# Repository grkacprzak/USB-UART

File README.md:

# USB-UART
industrial grade USB to UART converter

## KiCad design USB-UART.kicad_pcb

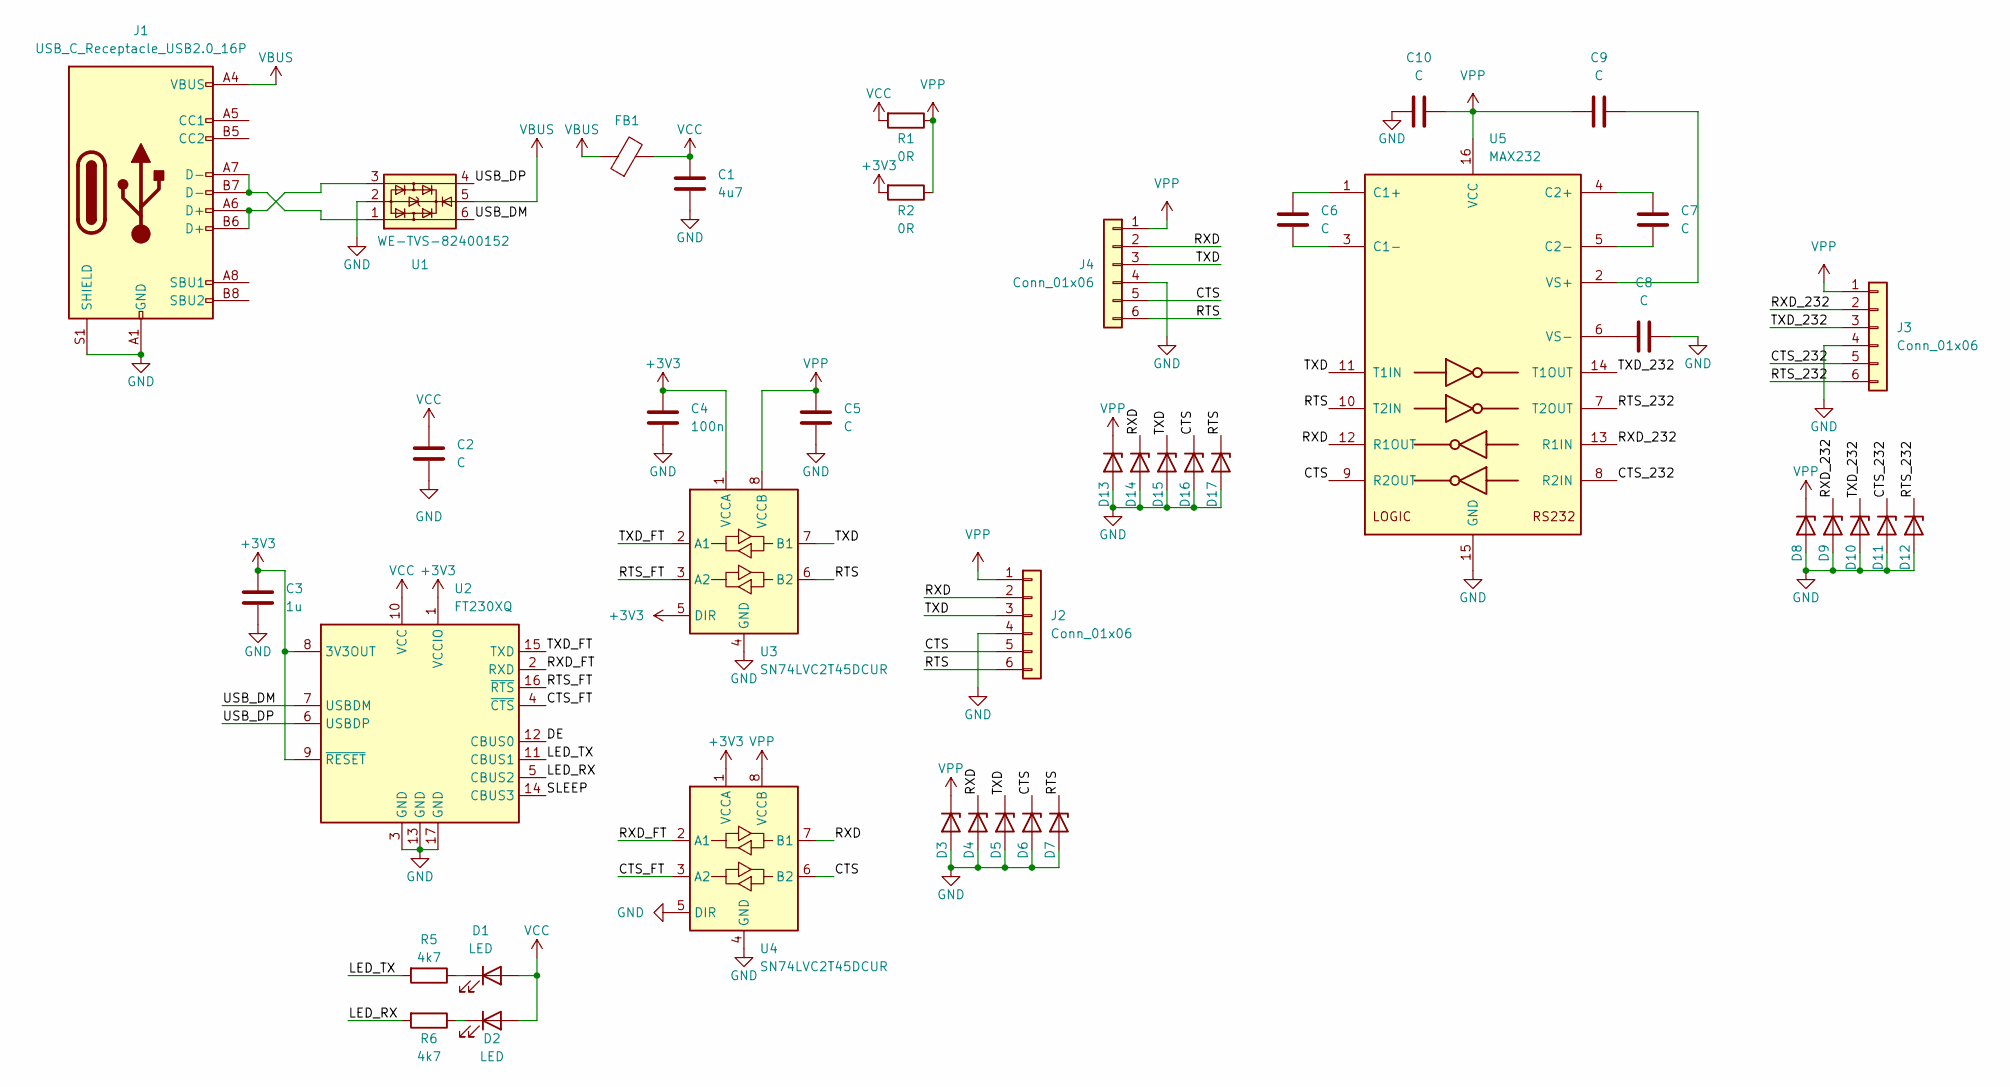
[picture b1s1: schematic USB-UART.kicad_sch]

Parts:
C1: 4u7; C_0402_1005Metric
C2, C5, C6, C7, C8, C9, C10: C; C_0402_1005Metric
C3: 1u; C_0402_1005Metric
C4: 100n; C_0402_1005Metric
D1, D2: LED; LED_0603_1608Metric
D3, D4, D5, D6, D7, D8, D9, D10, D11, D12, D13, D14, D15, D16, D17: D_Zener; D_SOD-523
FB1: FerriteBead; L_0402_1005Metric
J1: USB_C_Receptacle_USB2.0_16P; USB_C_Receptacle_Wuerth_629722000214
J2: Conn_01x06; PinHeader_1x06_P2.54mm_Horizontal
J3, J4: Conn_01x06; PinHeader_1x06_P2.54mm_Vertical
R1, R2: 0R; R_0402_1005Metric
R5, R6: 4k7; R_0402_1005Metric
U1: WE-TVS-82400152; SOT-563
U2: FT230XQ; QFN-16-1EP_4x4mm_P0.65mm_EP2.1x2.1mm
U3, U4: SN74LVC2T45DCUR; VSSOP-8_2.3x2mm_P0.5mm
U5: MAX232; TSSOP-16_4.4x5mm_P0.65mm

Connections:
+3V3: C3.1, C4.1, R2.2, U2.1 (VCCIO), U2.8 (3V3OUT), U2.9 (~RESET), U3.1 (VCCA), U3.5 (DIR), U4.1 (VCCA)
/CTS: D6.1 (K), D16.1 (K), J2.5, J4.5, U4.6 (B2), U5.9 (R2OUT)
/CTS_232: D11.1 (K), J3.5, U5.8 (R2IN)
/CTS_FT: U2.4 (~CTS), U4.3 (A2)
/DE: U2.12 (CBUS0)
/LED_RX: R6.2, U2.5 (CBUS2)
/LED_TX: R5.2, U2.11 (CBUS1)
/RTS: D7.1 (K), D17.1 (K), J2.6, J4.6, U3.6 (B2), U5.10 (T2IN)
/RTS_232: D12.1 (K), J3.6, U5.7 (T2OUT)
/RTS_FT: U2.16 (~RTS), U3.3 (A2)
/RXD: D4.1 (K), D14.1 (K), J2.2, J4.2, U4.7 (B1), U5.12 (R1OUT)
/RXD_232: D9.1 (K), J3.2, U5.13 (R1IN)
/RXD_FT: U2.2 (RXD), U4.2 (A1)
/SLEEP: U2.14 (CBUS3)
/TXD: D5.1 (K), D15.1 (K), J2.3, J4.3, U3.7 (B1), U5.11 (T1IN)
/TXD_232: D10.1 (K), J3.3, U5.14 (T1OUT)
/TXD_FT: U2.15 (TXD), U3.2 (A1)
/USB_DM: U1.6, U2.7 (USBDM)
/USB_DP: U1.4, U2.6 (USBDP)
GND: C1.2, C2.2, C3.2, C4.2, C5.2, C8.2, C10.1, D3.2 (A), D4.2 (A), D5.2 (A), D6.2 (A), D7.2 (A), D8.2 (A), D9.2 (A), D10.2 (A), D11.2 (A), D12.2 (A), D13.2 (A), D14.2 (A), D15.2 (A), D16.2 (A), D17.2 (A), J1.A1 (GND), J1.A12 (GND), J1.B1 (GND), J1.B12 (GND), J1.S1 (SHIELD), J2.4, J3.4, J4.4, U1.2, U2.3 (GND), U2.13 (GND), U2.17 (GND), U3.4 (GND), U4.4 (GND), U4.5 (DIR), U5.15 (GND)
unnamed: D1.1 (K), R5.1
unnamed: D2.1 (K), R6.1
unnamed: J1.A6 (D+), J1.B6 (D+), U1.3
unnamed: J1.A7 (D-), J1.B7 (D-), U1.1
unnamed: C6.1, U5.1 (C1+)
unnamed: C6.2, U5.3 (C1-)
unnamed: C7.1, U5.4 (C2+)
unnamed: C7.2, U5.5 (C2-)
unnamed: C9.2, U5.2 (VS+)
unnamed: C8.1, U5.6 (VS-)
VBUS: FB1.1, J1.A4 (VBUS), J1.A9 (VBUS), J1.B4 (VBUS), J1.B9 (VBUS), U1.5
VCC: C1.1, C2.1, D1.2 (A), D2.2 (A), FB1.2, R1.2, U2.10 (VCC)
VPP: C5.1, C9.1, C10.2, D3.1 (K), D8.1 (K), D13.1 (K), J2.1, J3.1, J4.1, R1.1, R2.1, U3.8 (VCCB), U4.8 (VCCB), U5.16 (VCC)

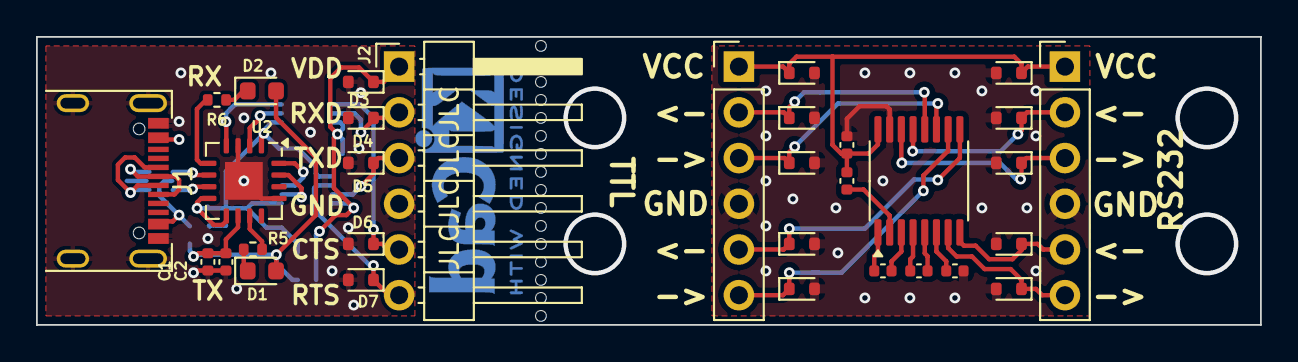
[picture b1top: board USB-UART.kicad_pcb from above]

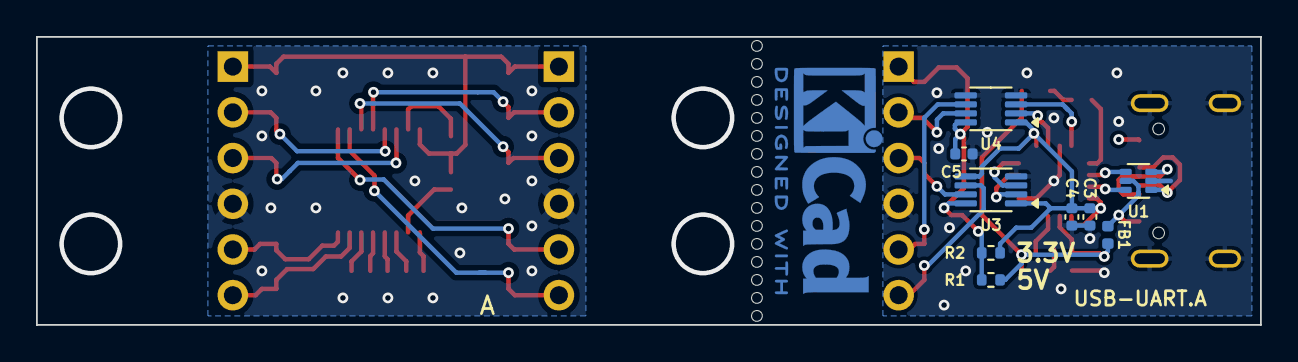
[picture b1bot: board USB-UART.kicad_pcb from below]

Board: 4 copper layers, 68.0 x 16.0 mm, 41 parts (9 on the bottom side), 31 nets.

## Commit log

2025-05-23 USB type A connector + brakable MAX232
2025-05-23 change connector to USBC
